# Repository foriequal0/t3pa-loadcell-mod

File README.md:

# Thrustmaster T3PA pedal load cell mod without a dead zone

Several prior works[^prior-works-1][^prior-works-2] replaced the existing potentiometer with a load cell. So there should be a physical dead zone until the pedal conacts the load cell, or the pedal's travel distance should be sacrificed by removing the gap.

I've solved the dead zone problem by integrating the existing potentiometer and a load cell.

[^prior-works-1]: [Thrustmaster T3PA Load Cell Mod - Falcon's Tech](https://www.youtube.com/watch?v=KIldeuIU-jM)
[^prior-works-2]: [Thrustmaster t3pa pedal Load Cell Mod | Simonas G](https://slowlogicboy.github.io/electronics/sim%20racing/TM-T3PA-LoadCellMod/)

There are three versions of the load cell mod in this repository.
If you want to make one, you should check out `v2` first.

* [v0](./t3pa-loadcell-mod-v0/README.md) : First prototype that is built by hand-soldering on a prototype board.
* [v1](./t3pa-loadcell-mod-v1/README.md) : It requires PCB manufacturing, but still hand-solderable.
* [v2](./t3pa-loadcell-mod-v2/README.md) : Successor of v1, the final version.

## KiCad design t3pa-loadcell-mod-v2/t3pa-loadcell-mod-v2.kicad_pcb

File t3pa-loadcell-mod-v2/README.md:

# v2

I've fixed my mistakes, again.

## v1's mistake

I abused `REF` pin as a voltage adder in v1 to simplify the circuit.
It worked fine, but it had a limited operating range.
When you apply more voltage to the `REF` pin, the output range starts to shrink,
so basically it had 1.8V ~ 2.0V range.

## Overview

```
   load cell ---> amplifier ---.
                              voltage adder ---> output
pedal ---> voltage follower ---`
```

Basically, back to the same configuration with v0, but with better components.

## Parts

* Load cell
  * CZL-611P 40kg
  * Wago 233-504, but KF141R would do the job.
* PCB
  * INA333AIDGKR
  * TLV9152IPWR
  * ES1J
  * 0805 SMD resistors, capacitors, optional tantalum caps.
* 3-pin JST-XH connectors
  * housing: XHP-3
  * header: B3B-XH-A/B3B-XH-AM
* and some mounting hardware
  * M6x2.1x27x35 Compression Spring Seat
  * M6xM10 thread inserts
  * M6x35 bolts, M6 nuts

## Details

Electrical details are the same with [v0](../t3pa-loadcell-mod-v0/README.md).
Physical details are the same with [v1](../t3pa-loadcell-mod-v1/README.md).

### Amplifier

I used INA333 because it has better parameters than AD623.
But I found later that TI says INA317 is an upgraded drop-in replacement of INA333.
Nevertheless, the circuits are designed with AD623 in mind.

They say AD623 (and INA333, INA317) has a rail-to-rail output.
But there's still very small output swing headroom (0.05V ~ 0.2V depending on the output current and the model),
and it is a quite noticeable when you're operating around the 0V.
So I applied ~0.4V voltage to `REF` pin with a simple voltage divider.
The datasheet says it should be driven by low impedance, but I didn't bother to use a voltage follower.

### Diode

Also, I used a diode to trim some voltage of the pedal.
The pedal's voltage range is already 1.8V ~ 3.3V.
With the 0.4V added to the `REF` pin, there's merely 1.1V of operating range left.
So I added ES1J diode to the pedal, which had a forward voltage of ~0.6V @ 0.01A.
It trimmed ~0.4V, which is less than I've expected, maybe because the current was too miniscule.

I also bought US1M, which has a forward voltage of ~0.8V @ 0.01A, but I didn't use it because I become lazy at this point.

## Photos

The load cell is not changed, see [v1](../t3pa-loadcell-mod-v1/README.md).

## Result

Slightly better than v1. I could say the project is finished.

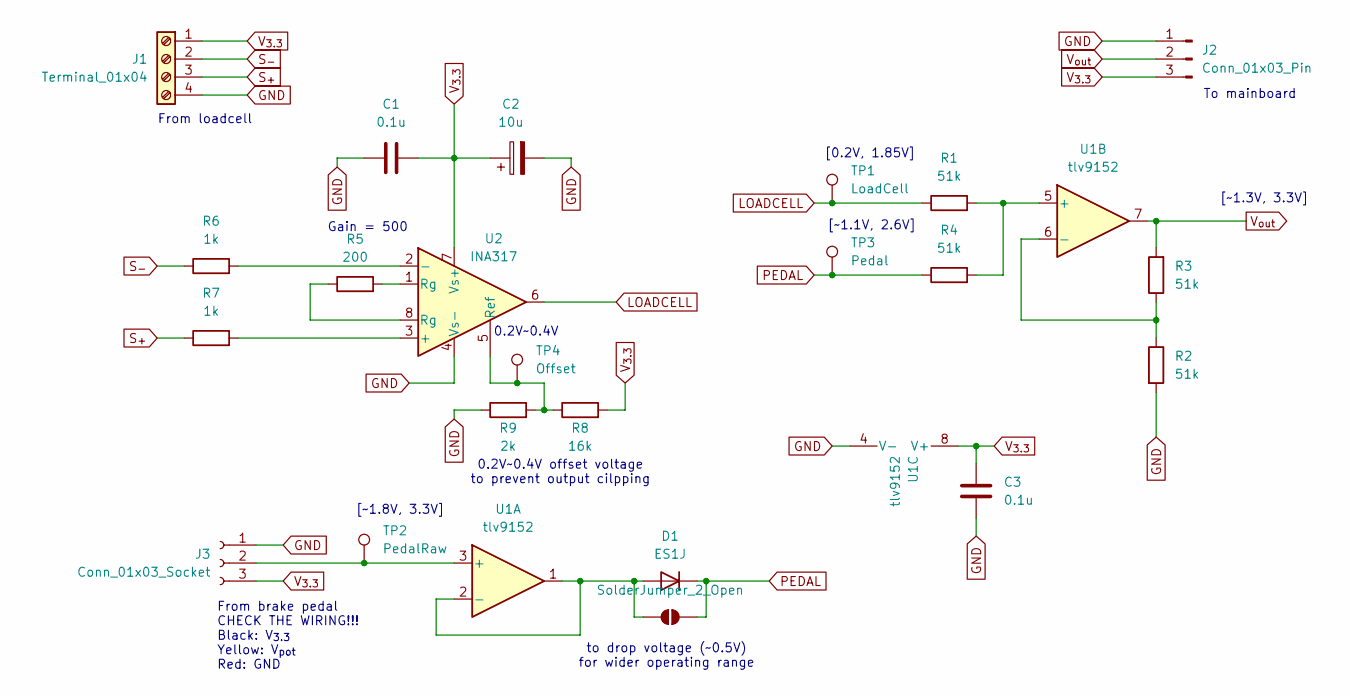
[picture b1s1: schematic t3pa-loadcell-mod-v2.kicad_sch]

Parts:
C1, C3: 0.1u; C_0805_2012Metric_Pad1.18x1.45mm_HandSolder
C2: 10u; CP_EIA-3216-10_Kemet-I_Pad1.58x1.35mm_HandSolder
D1: ES1J; D_SMA
J1: Terminal_01x04; TerminalBlock_WAGO_233-504_2x04_P2.54mm
J2: Conn_01x03_Pin; SolderWire-0.25sqmm_1x03_P4.2mm_D0.65mm_OD1.7mm
J3: Conn_01x03_Socket; JST_XH_B3B-XH-A_1x03_P2.50mm_Vertical
JP1: SolderJumper_2_Open; SolderJumper-2_P1.3mm_Open_RoundedPad1.0x1.5mm
R1, R2, R3, R4: 51k; R_0805_2012Metric_Pad1.20x1.40mm_HandSolder
R5: 200; R_0805_2012Metric_Pad1.20x1.40mm_HandSolder
R6, R7: 1k; R_0805_2012Metric_Pad1.20x1.40mm_HandSolder
R8: 16k; R_0805_2012Metric_Pad1.20x1.40mm_HandSolder
R9: 2k; R_0805_2012Metric_Pad1.20x1.40mm_HandSolder
TP1: LoadCell; TestPoint_Pad_D1.0mm
TP2: PedalRaw; TestPoint_Pad_D1.0mm
TP3: Pedal; TestPoint_Pad_D1.0mm
TP4: Offset; TestPoint_Pad_D1.0mm
U1: tlv9152; TSSOP-8_4.4x3mm_P0.65mm
U2: INA317; MSOP-8_3x3mm_P0.65mm

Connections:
GND: C1.1, C2.2, C3.2, J1.4, J2.1, J3.1, R2.2, R9.1, U1.4 (V-), U2.4 (Vs-)
LOADCELL: R1.1, TP1.1, U2.6
unnamed: D1.2 (A), JP1.1 (A), U1.1, U1.2 (-)
unnamed: J3.2, TP2.1, U1.3 (+)
unnamed: R5.1, U2.8 (Rg)
unnamed: R5.2, U2.1 (Rg)
unnamed: R1.2, R4.2, U1.5 (+)
unnamed: R2.1, R3.1, U1.6 (-)
unnamed: R7.2, U2.3 (+)
unnamed: R6.2, U2.2 (-)
unnamed: R8.1, R9.2, TP4.1, U2.5 (Ref)
PEDAL: D1.1 (K), JP1.2 (B), R4.1, TP3.1
S_{+}: J1.3, R7.1
S_{-}: J1.2, R6.1
V_{3.3}: C1.2, C2.1, C3.1, J1.1, J2.3, J3.3, R8.2, U1.8 (V+), U2.7 (Vs+)
V_{out}: J2.2, R3.2, U1.7

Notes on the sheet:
to drop voltage (~0.5V) for wider operating range
[~1.1V, 2.6V]
To mainboard
0.2V~0.4V
From loadcell
From brake pedal CHECK THE WIRING!!! Black: V_{3.3} Yellow: V_{pot} Red: GND
0.2V~0.4V offset voltage to prevent output cilpping
[0.2V, 1.85V]
[~1.3V, 3.3V]
Gain = 500
[~1.8V, 3.3V]

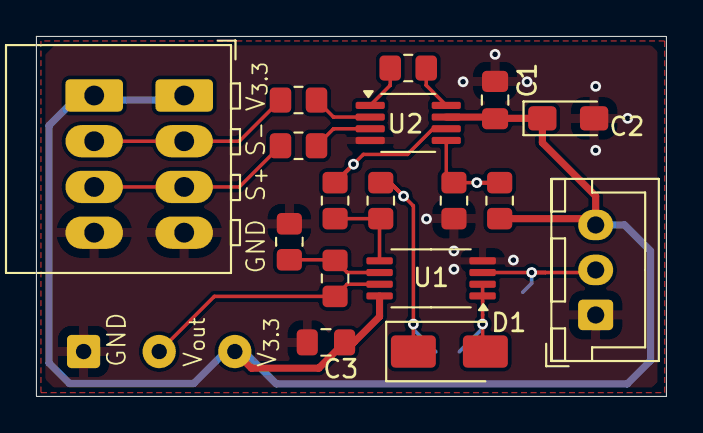
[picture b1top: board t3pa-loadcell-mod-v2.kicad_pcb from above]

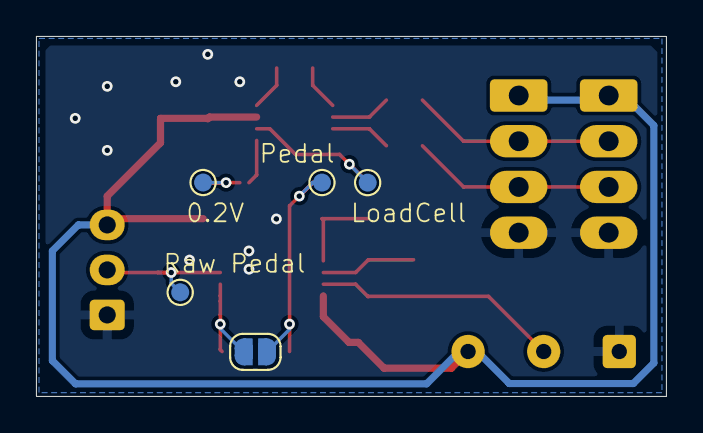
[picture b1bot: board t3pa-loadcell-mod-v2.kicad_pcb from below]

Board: 2 copper layers, 35.0 x 20.0 mm, 23 parts (5 on the bottom side), 16 nets.

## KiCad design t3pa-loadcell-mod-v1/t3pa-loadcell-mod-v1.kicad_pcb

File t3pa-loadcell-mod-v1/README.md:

# v1

I've designed a PCB for a better design. I've fixed my mistakes.

## Overview

The idea is simple: Use amplifier's REF pin to add the pedal's voltage.

## Parts

* Load cell
  * CZL-611P 40kg
  * Wago 233-504, but KF141R would do the job.
* PCB
  * AD623ARMZ
  * TLV9152IPWR
  * 0805 SMD resistors, capacitors, optional tantalum caps.
* 3-pin JST-XH connectors
  * housing: XHP-3
  * header: B3B-XH-A/B3B-XH-AM
* and some mounting hardware
  * M6x2.1x27x35 Compression Spring Seat
  * M6xM10 thread inserts
  * M6x35 bolts, M6 nuts

## Details

Electrical details are the same with [v0](../t3pa-loadcell-mod-v0/README.md).

### PCB

I've used AD620 before, but I've changed it to AD623 which has a rail-to-rail characteristics.
I've chosen 240 Ohm resistor to have 400x gain according to the datasheet.

While skimming through the datasheet, I've noticed Ref pin is used to control the output voltage offset. So I decided to abuse it to add the potentiometer.

I've ordered the PCB from [JLCPCB](https://jlcpcb.com/). Hand-soldering was not that hard.

### Mounting hardware

I've changed conical rubber shock absorber with M6x2.1x27x35 compression spring seat because why not? It can be mounted using M6 bolt. It has the right amount of compression force than the rubber shock absorber. I've removed the cap to reduce the height.

* [M6x2.1x27x35 compression spring seat - AliExpress](https://www.aliexpress.com/item/1005006497936423.html)

The rest is the same with the v0.

## Photos

## Result

Much better than v0. It's smaller, simpler, and less noisy.

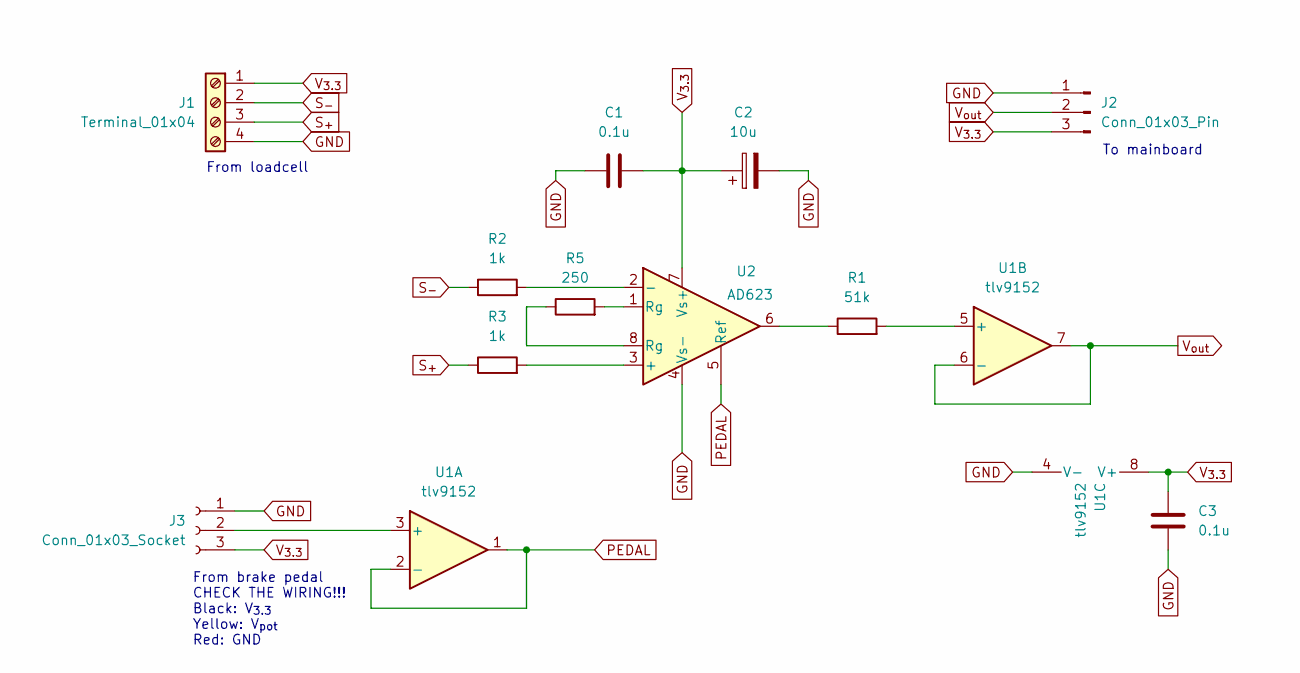
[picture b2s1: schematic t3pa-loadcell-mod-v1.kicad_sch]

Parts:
C1, C3: 0.1u; C_0805_2012Metric_Pad1.18x1.45mm_HandSolder
C2: 10u; CP_EIA-3216-10_Kemet-I_Pad1.58x1.35mm_HandSolder
J1: Terminal_01x04; TerminalBlock_WAGO_233-504_2x04_P2.54mm
J2: Conn_01x03_Pin; SolderWire-0.25sqmm_1x03_P4.2mm_D0.65mm_OD1.7mm
J3: Conn_01x03_Socket; JST_XH_B3B-XH-A_1x03_P2.50mm_Vertical
R1: 51k; R_0805_2012Metric_Pad1.20x1.40mm_HandSolder
R2, R3: 1k; R_0805_2012Metric_Pad1.20x1.40mm_HandSolder
R5: 250; R_0805_2012Metric_Pad1.20x1.40mm_HandSolder
U1: tlv9152; TSSOP-8_4.4x3mm_P0.65mm
U2: AD623; MSOP-8_3x3mm_P0.65mm

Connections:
GND: C1.1, C2.2, C3.2, J1.4, J2.1, J3.1, U1.4 (V-), U2.4 (Vs-)
unnamed: J3.2, U1.3 (+)
unnamed: R1.1, U2.6
unnamed: R5.1, U2.8 (Rg)
unnamed: R5.2, U2.1 (Rg)
unnamed: U1.1, U1.2 (-), U2.5 (Ref)
unnamed: R1.2, U1.5 (+)
unnamed: R3.2, U2.3 (+)
unnamed: R2.2, U2.2 (-)
S_{+}: J1.3, R3.1
S_{-}: J1.2, R2.1
V_{3.3}: C1.2, C2.1, C3.1, J1.1, J2.3, J3.3, U1.8 (V+), U2.7 (Vs+)
V_{out}: J2.2, U1.6 (-), U1.7

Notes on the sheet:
To mainboard
From loadcell
From brake pedal CHECK THE WIRING!!! Black: V_{3.3} Yellow: V_{pot} Red: GND

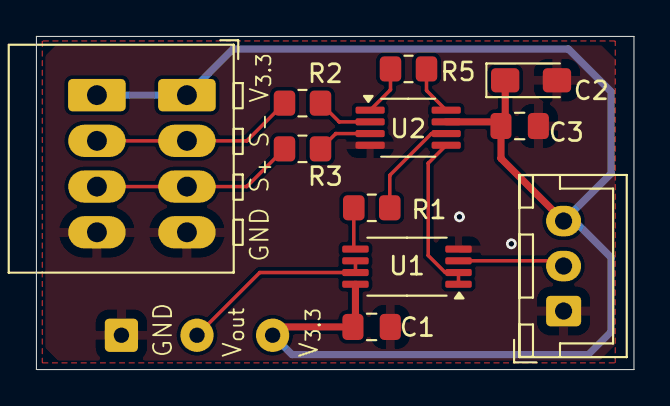
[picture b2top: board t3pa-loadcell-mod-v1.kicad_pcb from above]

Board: 2 copper layers, 33.2 x 18.5 mm, 12 parts (0 on the bottom side), 13 nets.

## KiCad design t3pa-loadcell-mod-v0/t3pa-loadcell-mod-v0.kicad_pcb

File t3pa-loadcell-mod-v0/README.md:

# v0: A prototype

I've built a prototype on a prototype board with a hand-soldering. I've made some mistakes, but it works fine.
PCB design included in the repo is a replica of the layout of the prototype.

## Overview

The idea is simple: Add voltages from two components with a voltage adder circuit.

## Parts

* Load cell
  * CZL-611P 40kg
  * 4-pin screw terminal block (5mm)
* Load cell amplifier
  * AD620 breakout module
  * 0603 (1608 metric) resistor (100 Ohm)
  * 1x4 female pin header (x2, 2.54mm pitch)
* Voltage adder
  * TLV272IP
  * 4 identical resistors (approx. 50k Ohm, 0.25W)
  * DIP-8 socket
* 3-pin JST-XH connectors
  * housing: XHP-3
  * header: B3B-XH-A/B3B-XH-AM
* and some mounting hardware
  * M6x18X20X25 conical rubber shock absorber
  * M6xM10 thread inserts
  * M6x35 bolts, M6 nuts

## Details

### The existing potentiometer

This is the measurement of potentiometers of mine:

|                | Gas   | Brake | Clutch |
| -------------- | ----- | ----- | ------ |
| V to GND (Ohm) | 24.8k | 21.9k |  24.0k |
| at rest (Ohm)  | 8.8k  | 12.0k |   9.7k |
| at full (Ohm)  | 24.8k | 21.9k |  24.0k |

I don't know why there are huge differences between the potentiometers, and how the wheel auto-calibrates,
but the important thing is that the voltage doesn't swing a whole range of 0V ~ 3.3V. The brake swings just from 1.8V to 3.3V.
So I have to tune the load cell amplifier to have a range of 1.5V.

Please check the wiring since it doesn't follow normal color codes. Mine was black for 3.3V, red for GND, and yellow for voltage output.

### CZL-611P 40kg

I bought it from [AliExpress](https://ko.aliexpress.com/item/1005007928954675.html). 50kg one arrived (it doesn't matter for the application).

The store page says the output sensitivity is '10 ± 0.1mVN', but I think it is a typo. Some other websites say it is '1.0 ± 0.1mV/V'.
So, the output voltage difference at full load (50kg) will be 3.3mV because the given excitation voltage is 3.3V.
To get an approx. 1.5V output range, we need a gain of approx. 450x.
If we need an output range of 1.3V, the gain will be approx. 400x.

I've cut the first screw hole part out with a hand saw to reduce interference when installing.

### AD620 breakout module

I've bought AD620 breakout modules by mistake instead of AD623. I didn't know its limited output range (V_in - 2.0V).
Luckily ~1.3V range is somewhat enough for this project (the first 0.2V range will be covered by the potentiometer)

You can buy it and get more information about it from [Proto Supplies](https://protosupplies.com/product/ad620-instrumentation-amplifier-module/).
Or you could get cheaper clones from AliExpress instead. It seems that there are several versions of it on Aliexpress. The module's dimension that I've used is 32mm * 22mm.

To get a gain of 400x, I've changed its 100K trimmer potentiometer with a fixed 120 Ohm resistor by following the Proto Supplies' guide (R_gain = 49.9K / (Gain -1).
After that, I adjusted the zero offset with the load cell connected.

You shouldn't remove 7660 since it seems necessary to our application's range.

### TLV272IP

I bought LM358 at first because AD620 module used it, and I discovered that it heavily clips the output voltage (maximum output is approx. 2.0V out of 3.3V) too late.
It might be the reason why AD620 breakout module's range is limited and it needs 7660!
Luckily, I found a StackExchange answer that suggested a rail-to-rail op-amp such as TLV27x series[^stackexchange].
It is pin-to-pin compatible with LM358, so I've bought TLV272IP.
It was a good idea to use DIP-8 socket instead of directly soldering LM358 to the board.

[^stackexchange]: https://electronics.stackexchange.com/a/357054

Exact resistor values don't matter unless they are large (10k~100k Ohm), and relatively equal to each other (R1 = R2, R3 = R4). I've actually picked R1 = R2 = 51k, R3 = R4 = 47k.

### Mounting hardware

I bought M6x18X20X25 conical rubber shock absorber because CZL-611P has M6 threaded holes.

* [M6x18X20X25 - AliExpress](https://www.aliexpress.com/item/1005005386072058.html)

I've used a M6xM10 threaded insert since T3PA's bracket has M10 threaded hole while CZL-611P has M6 threaded hole. I bought 10mm length one, but 12mm or 15mm one would've been nicer to work with.
A M10 nut that is included in T3PA's bracket mod kit is used to lock the threaded insert to the bracket.
M6x35 bolt, M6 nuts to mount CZL-611 onto the bracket.

* [M6xM10 threaded insert - AliExpress](https://www.aliexpress.com/item/1005006827476112.html)

## Photos

Here are some photos of the prototype board.

1. Removed gain trimmer potentiometer.
2. Installed 120 Ohm resistor (metric 1608, imperial 0603)
3. The connector from the existing potentiometer. Don't be fooled by wiring colors.
4. From the potentiometer.
5. To the mainboard of the pedal.
6. The range that is covered by the potentiometer.
7. The range that is covered by the load cell.

## Result

You can control the brakes delicately as you could before in the potentiometer range.
In the load cell range, you can feel the physical resistance when you hit the brakes hard while not losing controllability.
The transition between the potentiometer and the load cell is smooth as expected although the output is a little bit noisier than before.

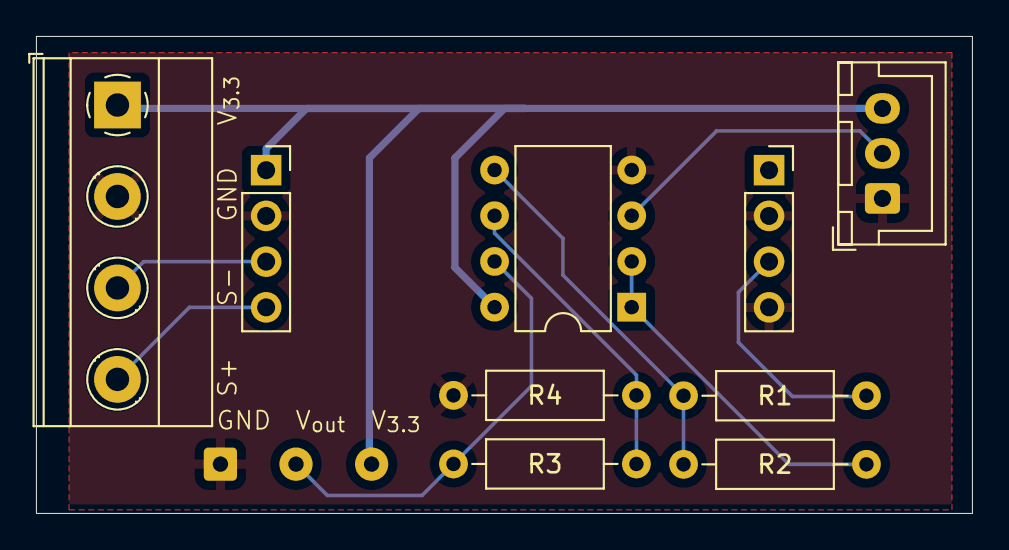
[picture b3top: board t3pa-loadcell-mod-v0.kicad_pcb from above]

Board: 2 copper layers, 52.0 x 26.5 mm, 10 parts (0 on the bottom side), 10 nets.

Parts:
J1: Screw_Terminal_01x04; TerminalBlock_Phoenix_MKDS-1,5-4-5.08_1x04_P5.08mm_Horizont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
J2: Conn_01x03_Pin; SolderWire-0.25sqmm_1x03_P4.2mm_D0.65mm_OD1.7mm
J3: Conn_01x03_Socket; JST_XH_B3B-XH-A_1x03_P2.50mm_Vertical
J4, J5: Conn_01x04_Pin; PinSocket_1x04_P2.54mm_Vertical
R1, R2, R3, R4: 51k; R_Axial_DIN0207_L6.3mm_D2.5mm_P10.16mm_Horizontal
U1: TLV272IP; DIP-8_W7.62mm

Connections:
/AD620 module/S_{+}: J1.4, J4.4
/AD620 module/S_{-}: J1.3, J4.3
/AD620 module/V_{out}: J5.3, R1.1
GND: J1.2, J2.1, J3.1, J4.2, J5.2, J5.4, R4.1, U1.4 (V-)
unnamed: J3.2, U1.3 (+)
unnamed: R2.2, U1.1, U1.2 (-)
unnamed: R1.2, R2.1, U1.5 (+)
unnamed: R3.1, R4.2, U1.6 (-)
V_{3.3}: J1.1, J2.3, J3.3, J4.1, U1.8 (V+)
V_{out}: J2.2, R3.2, U1.7

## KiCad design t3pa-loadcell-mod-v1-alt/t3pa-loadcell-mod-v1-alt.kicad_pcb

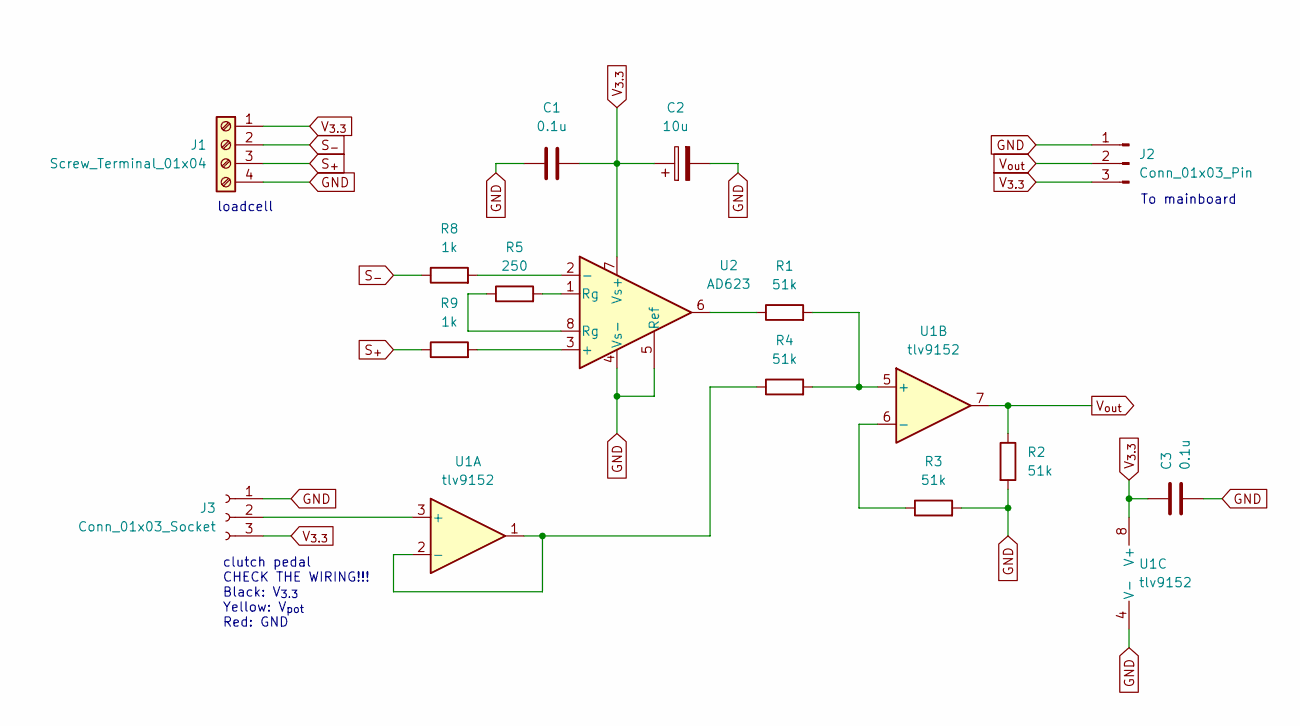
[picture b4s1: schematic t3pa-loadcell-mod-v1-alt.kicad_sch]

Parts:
C1, C3: 0.1u; C_0805_2012Metric_Pad1.18x1.45mm_HandSolder
C2: 10u; CP_EIA-3216-10_Kemet-I_Pad1.58x1.35mm_HandSolder
J1: Screw_Terminal_01x04; TerminalBlock_Phoenix_MKDS-1,5-4-5.08_1x04_P5.08mm_Horizont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
J2: Conn_01x03_Pin; SolderWire-0.25sqmm_1x03_P4.2mm_D0.65mm_OD1.7mm
J3: Conn_01x03_Socket; JST_XH_B3B-XH-A_1x03_P2.50mm_Vertical
R1, R2, R3, R4: 51k; R_0805_2012Metric_Pad1.20x1.40mm_HandSolder
R5: 250; R_0805_2012Metric_Pad1.20x1.40mm_HandSolder
R8, R9: 1k; R_0805_2012Metric_Pad1.20x1.40mm_HandSolder
U1: tlv9152; TSSOP-8_3x3mm_P0.65mm
U2: AD623; MSOP-8_3x3mm_P0.65mm

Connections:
GND: C1.1, C2.2, C3.2, J1.4, J2.1, J3.1, R2.2, R3.2, U1.4 (V-), U2.4 (Vs-), U2.5 (Ref)
unnamed: J3.2, U1.3 (+)
unnamed: R1.1, U2.6
unnamed: R5.1, U2.8 (Rg)
unnamed: R5.2, U2.1 (Rg)
unnamed: R4.1, U1.1, U1.2 (-)
unnamed: R1.2, R4.2, U1.5 (+)
unnamed: R3.1, U1.6 (-)
unnamed: R9.2, U2.3 (+)
unnamed: R8.2, U2.2 (-)
S_{+}: J1.3, R9.1
S_{-}: J1.2, R8.1
V_{3.3}: C1.2, C2.1, C3.1, J1.1, J2.3, J3.3, U1.8 (V+), U2.7 (Vs+)
V_{out}: J2.2, R2.1, U1.7

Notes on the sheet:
To mainboard
loadcell
clutch pedal CHECK THE WIRING!!! Black: V_{3.3} Yellow: V_{pot} Red: GND

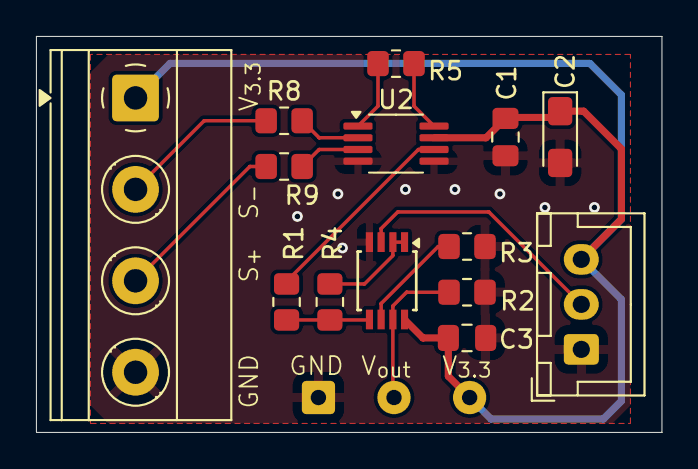
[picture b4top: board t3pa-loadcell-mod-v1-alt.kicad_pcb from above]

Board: 2 copper layers, 34.8 x 22.0 mm, 15 parts (0 on the bottom side), 14 nets.

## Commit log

2025-03-01 Update v0
2025-03-01 Update v1
2025-03-29 Update gitignore
2025-03-29 Add v1-alt
2025-07-06 Add v2
